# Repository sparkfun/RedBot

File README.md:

SparkFun RedBot
===============

<table class="table table-hover table-striped table-bordered">
  <tr align="center">
   <td></td>
   <td></td>
  </tr>
  <tr align="center">
    <td>RedBot Mainboard [<a href="https://www.sparkfun.com/products/12097">ROB-12097</a>]</td>
    <td>SparkFun Inventor's Kit for RedBot [<a href="https://www.sparkfun.com/products/12649">ROB-12649</a>]</td>
  </tr>
</table>

Design files and firmware files for the [RedBot Main board](https://www.sparkfun.com/products/11622).

Repository Contents
-------------------

* **/Documentation** - Documentation for the library's public API
* **/Hardware** - Eagle PCB layout files
* **/Libraries/Arduino/RedBot** - RedBot support library
* **/Production** - Files to support SparkFun production

Documentation
--------------

* **[Installing an Arduino Library Guide](https://learn.sparkfun.com/tutorials/installing-an-arduino-library)** - Basic information on how to install an Arduino library.
* **[Product Repository](https://github.com/sparkfun/RedBot)** - Main repository (including hardware files) for the RedBot.
* **[Library Repository](https://github.com/sparkfun/SparkFun_Redbot_Arduino_Library)** - Arduino library for the RedBot.
* **[Assembly Guide](https://learn.sparkfun.com/tutorials/assembly-guide-for-redbot-with-shadow-chassis)** - Basic hookup guide for the RedBot.
* **[Experiment Guide](https://learn.sparkfun.com/tutorials/experiment-guide-for-redbot-with-shadow-chassis)** - Experiment guide for the RedBot.

Product Versions
----------------
This repository only contains the hardware files for the RedBot Main board. There are several different support products available for the RedBot Kit however.

* [ROB-12097](https://www.sparkfun.com/products/12097) - RedBot Main Board.
* [ROB-12649](https://www.sparkfun.com/products/12649) - RedBot SparkFun Inventor's Kit
* *[ROB-13166 (RETIRED)](https://www.sparkfun.com/products/13166) - RedBot Basic Kit*
* [ROB-12567](https://www.sparkfun.com/products/12567) - RedBot Buzzer
* [SEN-11999](https://www.sparkfun.com/products/11999) - RedBot Mechanical Bumper
* [SEN-12589](https://www.sparkfun.com/products/12589) - RedBot Accelerometer
* [SEN-11769](https://www.sparkfun.com/products/11769) - RedBot Line Sensor
* [SEN-13582](https://www.sparkfun.com/products/13582) - SparkFun Line Follower Array

License Information
-------------------

This product is _**open source**_! 

Please review the LICENSE.md file for license information. 

If you have any questions or concerns on licensing, please contact techsupport@sparkfun.com.

Distributed as-is; no warranty is given.

- Your friends at SparkFun.

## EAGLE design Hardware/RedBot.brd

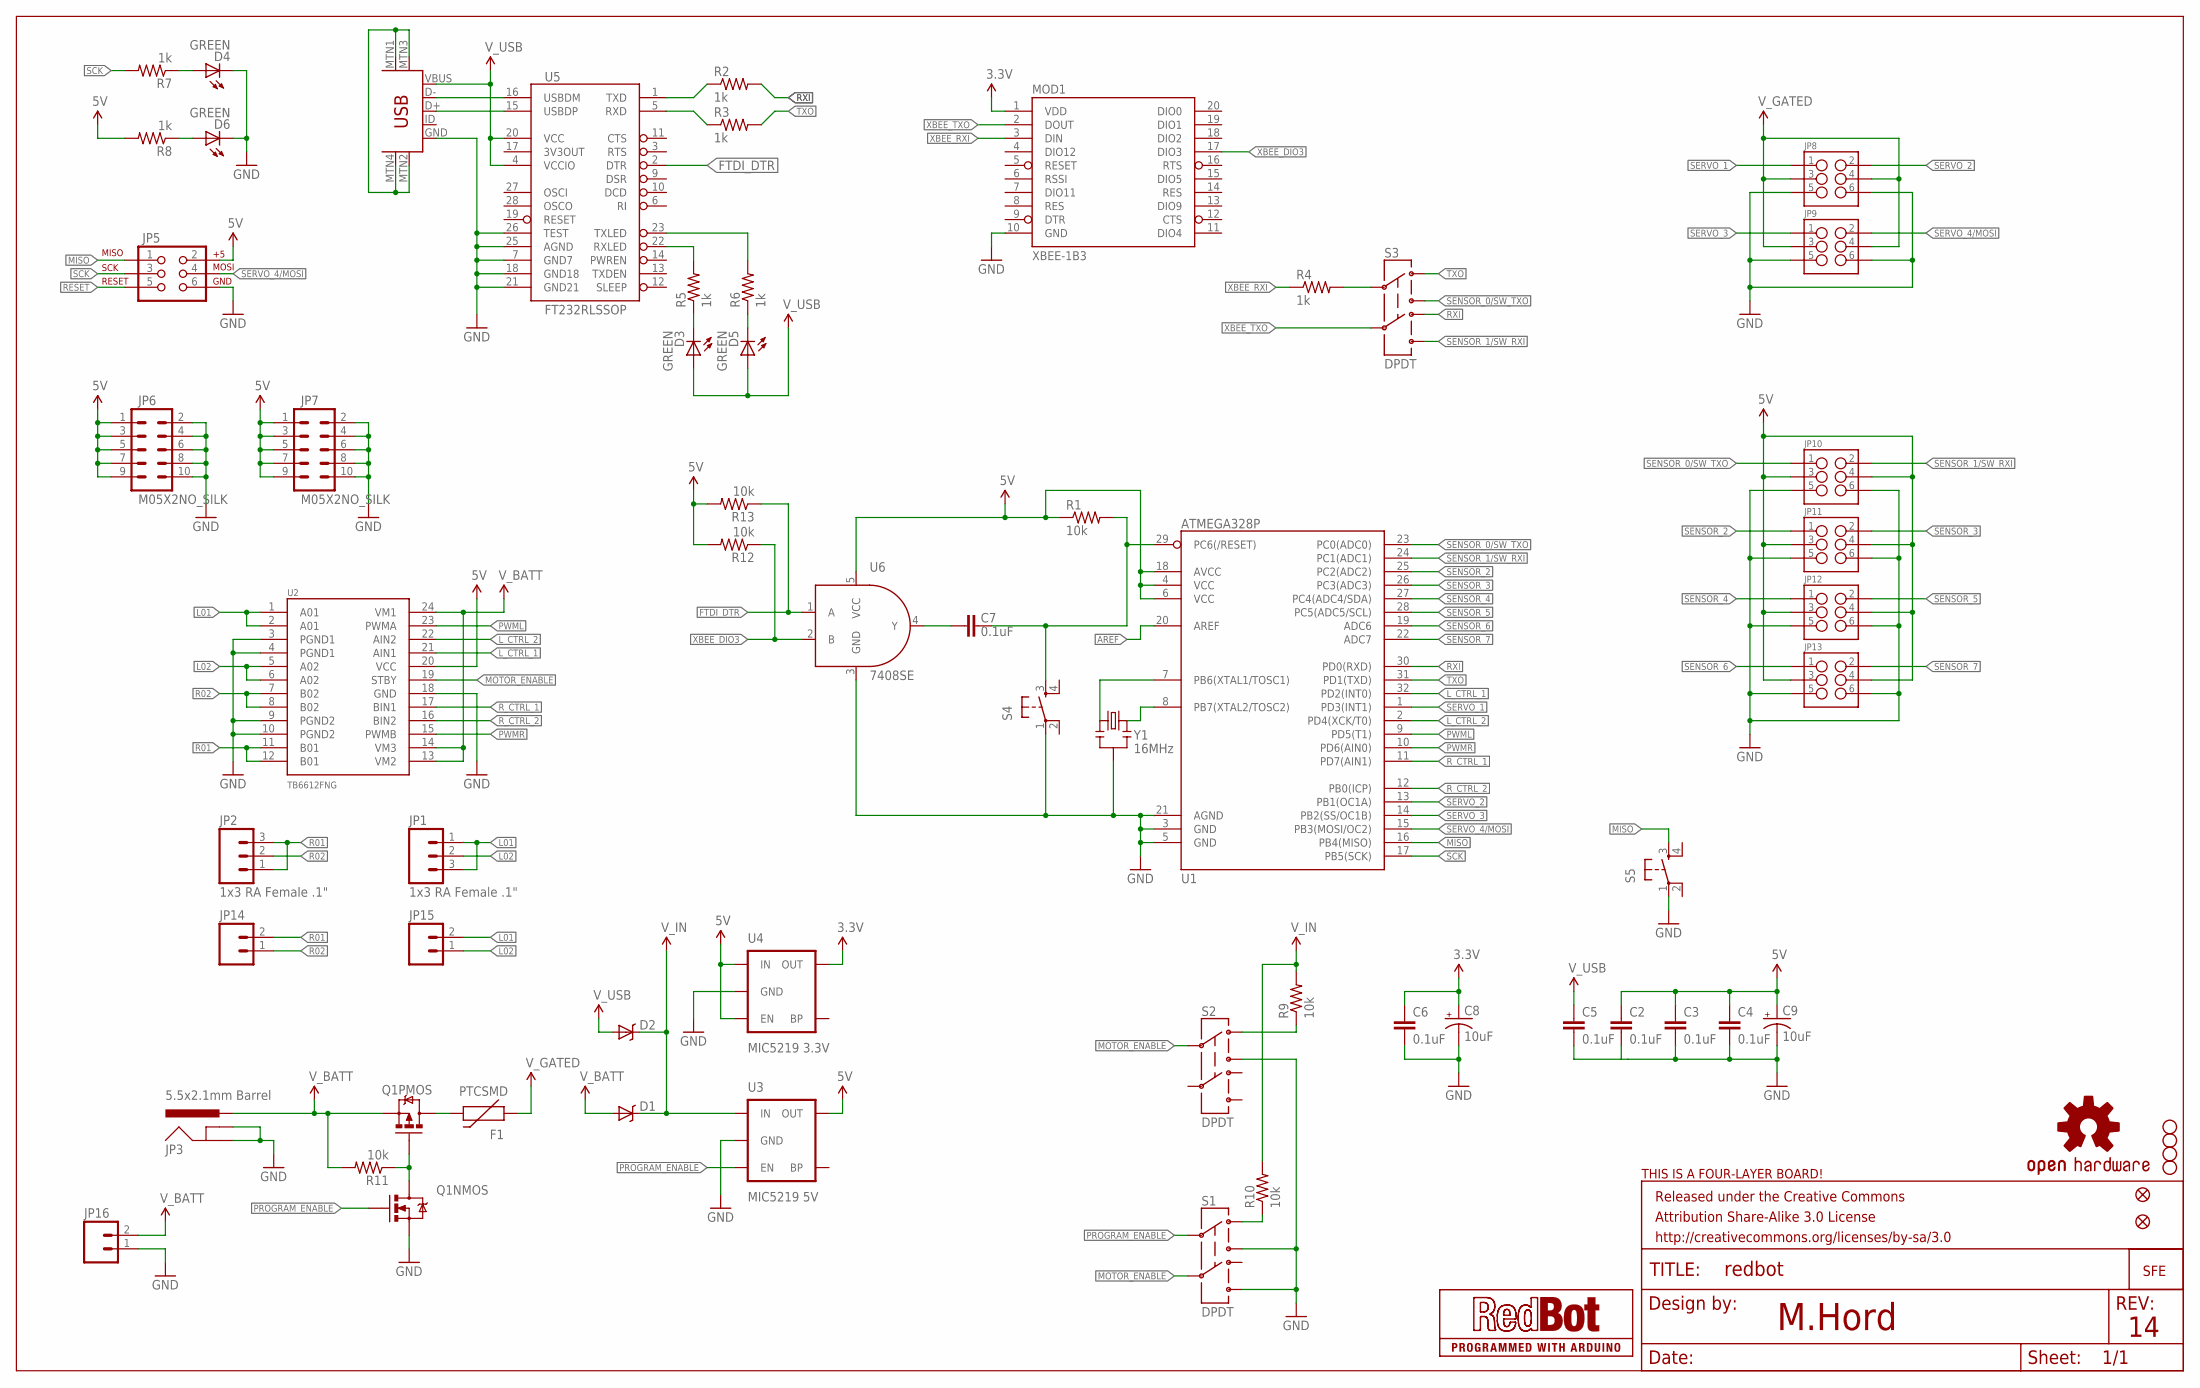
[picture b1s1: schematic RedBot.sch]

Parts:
C2, C3, C4, C5, C6, C7: 0.1uF; 0603-CAP
C8, C9: 10uF; EIA3216
D1, D2: B340A; SMA-DIODE
D3, D4, D5, D6: GREEN; LED-0603
F1: PTCSMD; PTC-1206
FID1, FID2: FIDUCIALUFIDUCIAL; MICRO-FIDUCIAL
FRAME1: FRAME-LETTER; CREATIVE_COMMONS
JP1, JP2: 1x3 RA Female .1"; 1X03_SMD_RA_FEMALE
JP3: 5.5x2.1mm Barrel; POWER_JACK_SMD
JP4: USB-B; USB-MINIB
JP5: AVR_SPI_PRG_6PTH; 2X3
JP6, JP7: M05X2NO_SILK; 2X5_NOSILK
JP8, JP9, JP10, JP11, JP12, JP13: M03X2SMT; 2X3_SMT_POSTS
JP14, JP15, JP16: M02PTH; 1X02
MOD1: XBEE-1B3; XBEE-SMD
Q1: IRF7509; MSOP8
R1, R9, R10, R11, R12, R13: 10k; 0603-RES
R2, R3, R4, R5, R6, R7, R8: 1k; 0603-RES
S1, S2, S3: DPDT; AYZ0202
S4, S5: TAC_SWITCHSMD; TACTILE_SWITCH_SMD
SFE-LOGO1: LOGO-SFENEW; SFE-NEW-WEBLOGO
STANDOFF1, STANDOFF2, STANDOFF3, STANDOFF4: STAND-OFF
U1: ATMEGA328P; TQFP32-08
U2: TB6612FNG; SSOP24
U3: MIC5219 5V; SOT23-5
U4: MIC5219 3.3V; SOT23-5
U5: FT232RLSSOP; SSOP28DB
U6: 7408SE; SOT353
U$17: OSHW-LOGOS; OSHW-LOGO-S
U$21: FOUR_LAYER_WARNING
U$23: REDBOT_LOGO
Y1: 16MHz; RESONATOR-SMD

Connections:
3.3V: C6.1, C8.A (+), MOD1.1 (VDD), U4.5 (OUT)
5V: C2.1, C3.1, C4.1, C9.A (+), JP5.2, JP6.1, JP6.3, JP6.5, JP6.7, JP6.9, JP7.1, JP7.3, JP7.5, JP7.7, JP7.9, JP10.3, JP10.4, JP11.3, JP11.4, JP12.3, JP12.4, JP13.3, JP13.4, R1.1, R8.2, R12.2, R13.2, U1.4 (VCC), U1.6 (VCC), U1.18 (AVCC), U2.20 (VCC), U3.5 (OUT), U4.1 (IN), U4.3 (EN), U6.5 (VCC)
AREF: U1.20 (AREF)
FT232_RXI: R3.1, U5.5 (RXD)
FT232_TXO: R2.1, U5.1 (TXD)
FTDI_DTR: R13.1, U5.2 (DTR), U6.1 (A)
GND: C2.2, C3.2, C4.2, C5.2, C6.2, C8.C (-), C9.C (-), D4.C, D6.C, JP3.GND (GNDBREAK), JP3.P$4 (GND), JP4.GND, JP5.6, JP6.2, JP6.4, JP6.6, JP6.8, JP6.10, JP7.2, JP7.4, JP7.6, JP7.8, JP7.10, JP8.5, JP8.6, JP9.5, JP9.6, JP10.5, JP10.6, JP11.5, JP11.6, JP12.5, JP12.6, JP13.5, JP13.6, JP16.1, MOD1.10 (GND), Q1.1 (S), S1.3, S1.6, S2.3, S4.1, S5.1, U1.3 (GND), U1.5 (GND), U1.21 (AGND), U2.3 (PGND1), U2.4 (PGND1), U2.9 (PGND2), U2.10 (PGND2), U2.18 (GND), U3.2 (GND), U4.2 (GND), U5.7 (GND7), U5.18 (GND18), U5.21 (GND21), U5.25 (AGND), U5.26 (TEST), U6.3 (GND), Y1.2
L01: JP1.1, JP1.3, JP15.2, U2.1 (A01), U2.2 (A01)
L02: JP1.2, JP15.1, U2.5 (A02), U2.6 (A02)
L_CTRL_1: U1.32 (PD2(INT0)), U2.21 (AIN1)
L_CTRL_2: U1.2 (PD4(XCK/T0)), U2.22 (AIN2)
MISO: JP5.1, S5.3, U1.16 (PB4(MISO))
MOTOR_ENABLE: S1.5, S2.2, U2.19 (STBY)
unnamed: R4.2, S3.2
unnamed: Q1.4 (G), Q1.7 (D), Q1.8 (D), R11.1
unnamed: D5.C, R6.1
unnamed: D3.C, R5.1
unnamed: C7.2, U6.4 (Y)
unnamed: JP4.MTN1 (MTN2), JP4.MTN2 (MTN3), JP4.MTN3 (MTN1), JP4.MTN4
unnamed: D4.A, R7.1
unnamed: D6.A, R8.1
unnamed: F1.2, Q1.5 (D), Q1.6 (D)
unnamed: R9.1, S2.1
unnamed: U1.8 (PB7(XTAL2/TOSC2)), Y1.3
unnamed: U1.7 (PB6(XTAL1/TOSC1)), Y1.1
unnamed: JP4.D-, U5.16 (USBDM)
unnamed: JP4.D+, U5.15 (USBDP)
PG_EN: R10.1, S1.1
PROGRAM_ENABLE: Q1.2 (G), S1.2, U3.3 (EN)
PWML: U1.9 (PD5(T1)), U2.23 (PWMA)
PWMR: U1.10 (PD6(AIN0)), U2.15 (PWMB)
R01: JP2.1, JP2.3, JP14.2, U2.11 (B01), U2.12 (B01)
R02: JP2.2, JP14.1, U2.7 (B02), U2.8 (B02)
RESET: C7.1, JP5.5, R1.2, S4.3, U1.29 (PC6(/RESET))
RXI: R2.2, S3.4, U1.30 (PD0(RXD))
RXLED: R5.2, U5.22 (RXLED)
R_CTRL_1: U1.11 (PD7(AIN1)), U2.17 (BIN1)
R_CTRL_2: U1.12 (PB0(ICP)), U2.16 (BIN2)
SCK: JP5.3, R7.2, U1.17 (PB5(SCK))
SENSOR_0/SW_TXO: JP10.1, S3.3, U1.23 (PC0(ADC0))
SENSOR_1/SW_RXI: JP10.2, S3.6, U1.24 (PC1(ADC1))
SENSOR_2: JP11.1, U1.25 (PC2(ADC2))
SENSOR_3: JP11.2, U1.26 (PC3(ADC3))
SENSOR_4: JP12.1, U1.27 (PC4(ADC4/SDA))
SENSOR_5: JP12.2, U1.28 (PC5(ADC5/SCL))
SENSOR_6: JP13.1, U1.19 (ADC6)
SENSOR_7: JP13.2, U1.22 (ADC7)
SERVO_1: JP8.1, U1.1 (PD3(INT1))
SERVO_2: JP8.2, U1.13 (PB1(OC1A))
SERVO_3: JP9.1, U1.14 (PB2(SS/OC1B))
SERVO_4/MOSI: JP5.4, JP9.2, U1.15 (PB3(MOSI/OC2))
TXLED: R6.2, U5.23 (TXLED)
TXO: R3.2, S3.1, U1.31 (PD1(TXD))
V_BATT: D1.A, JP3.VIN0 (PWR), JP16.2, Q1.3 (S), R11.2, U2.13 (VM2), U2.14 (VM3), U2.24 (VM1)
V_GATED: F1.1, JP8.3, JP8.4, JP9.3, JP9.4
V_IN: D1.C, D2.C, R9.2, R10.2, U3.1 (IN)
V_USB: C5.1, D2.A, D3.A, D5.A, JP4.VBUS, U5.4 (VCCIO), U5.20 (VCC)
XBEE_DIO3: MOD1.17 (DIO3), R12.1, U6.2 (B)
XBEE_RXI: MOD1.3 (DIN), R4.1
XBEE_TXO: MOD1.2 (DOUT), S3.5

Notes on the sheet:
M.Hord

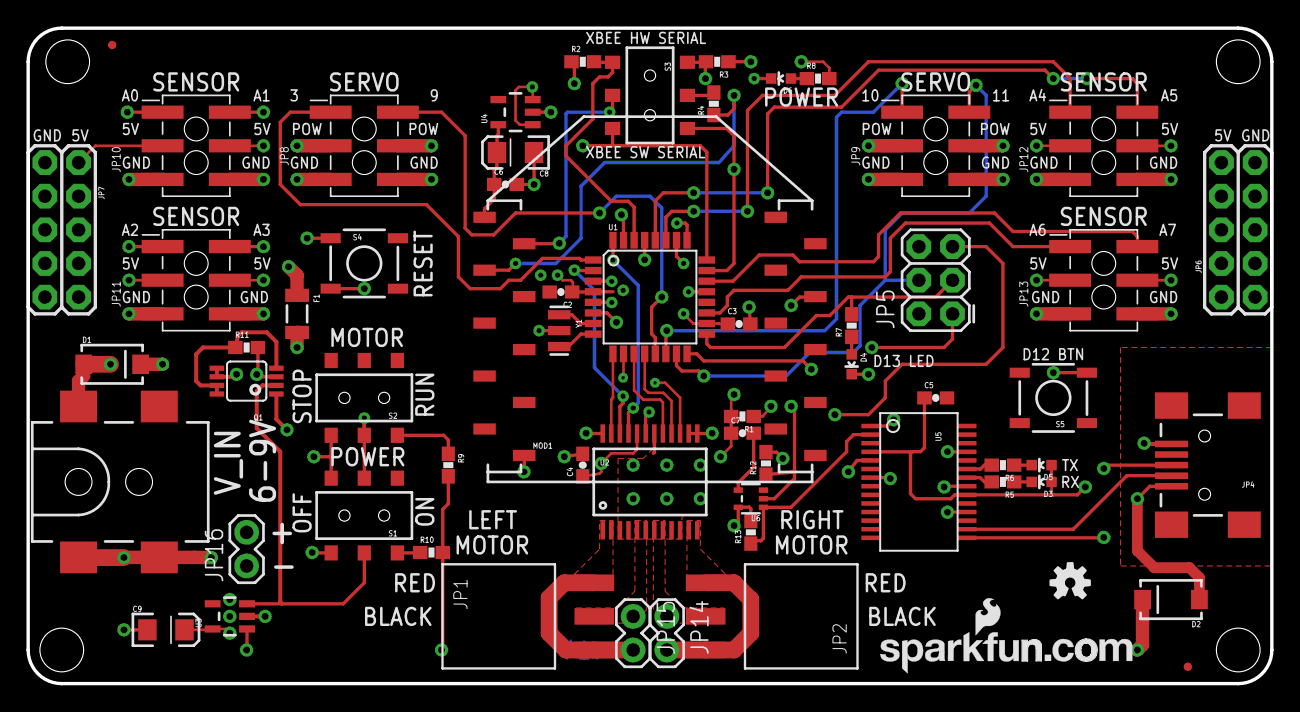
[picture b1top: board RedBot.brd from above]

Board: 4 copper layers, 94.0 x 49.5 mm, 69 parts (1 on the bottom side), 59 nets.

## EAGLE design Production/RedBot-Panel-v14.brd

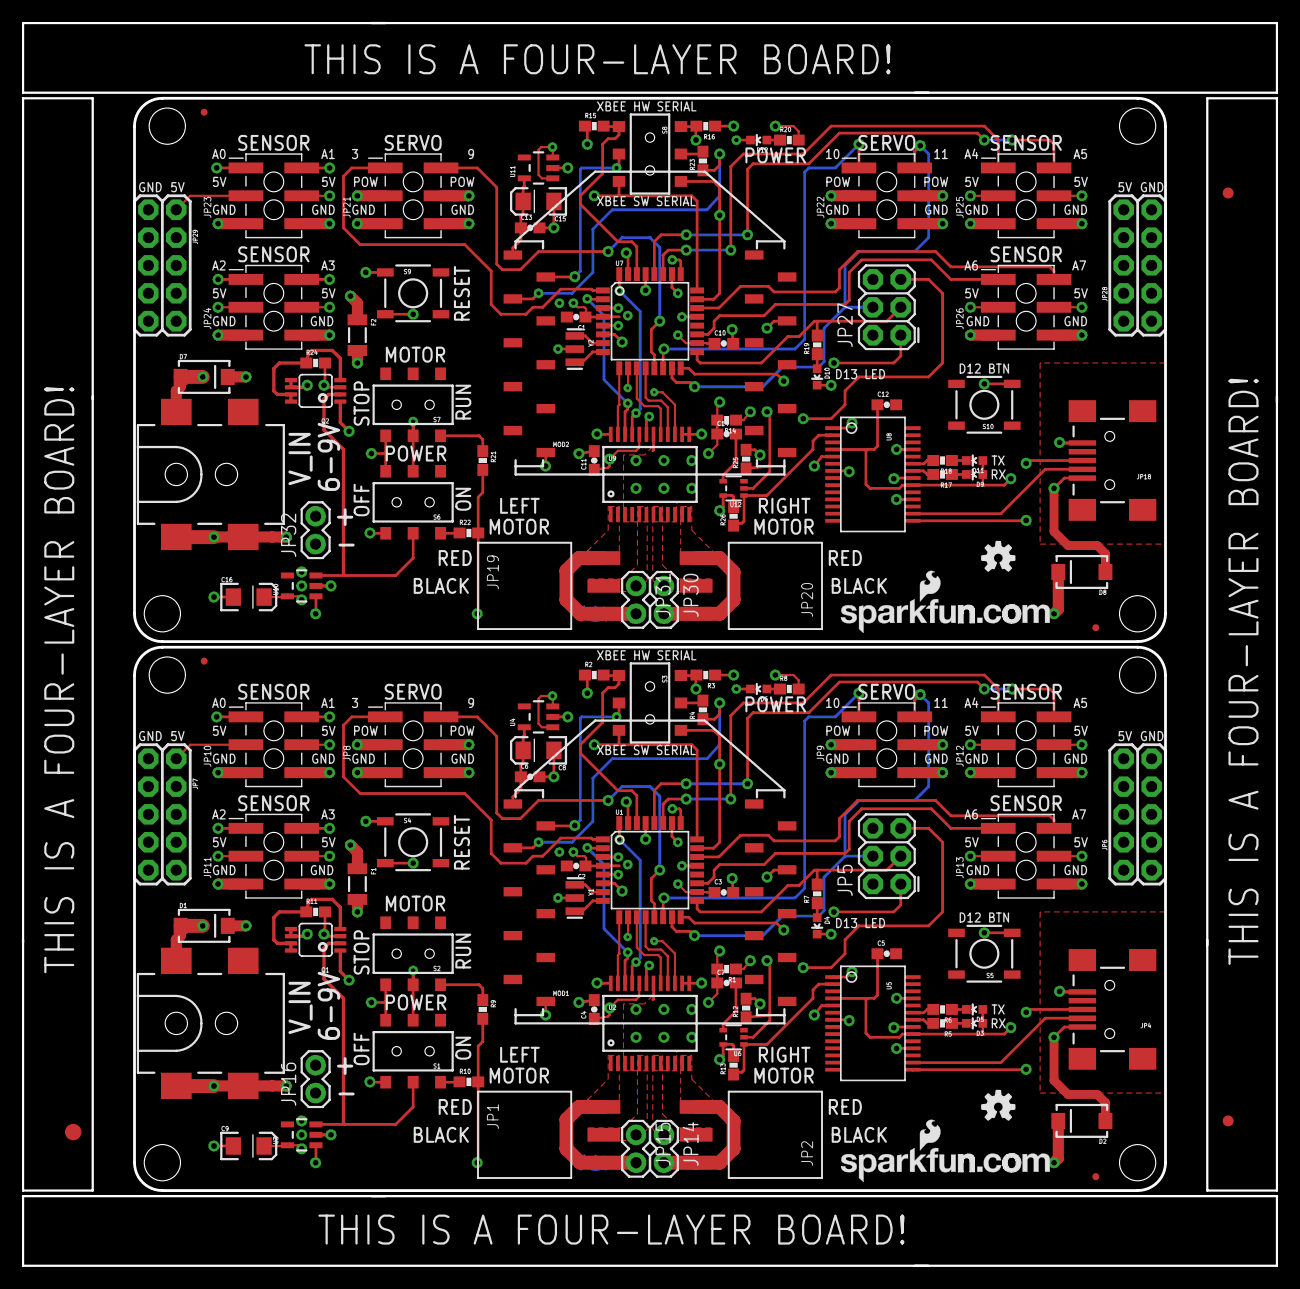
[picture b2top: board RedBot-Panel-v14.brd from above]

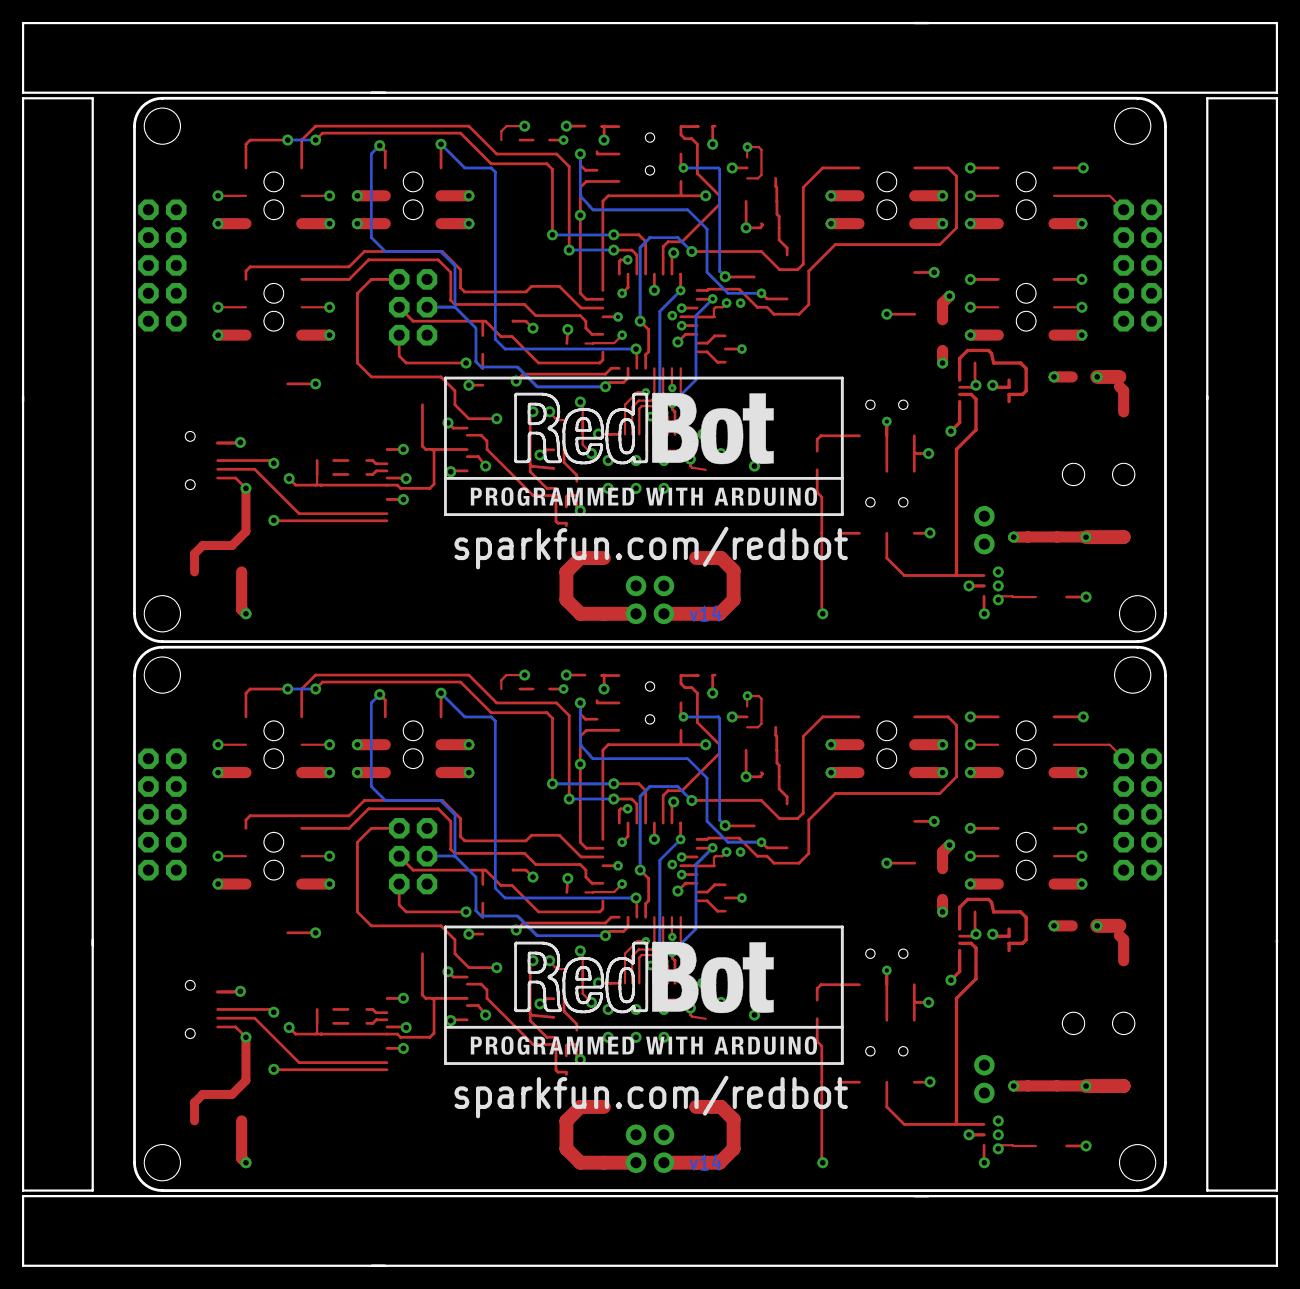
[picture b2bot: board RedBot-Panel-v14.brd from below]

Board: 4 copper layers, 114.3 x 113.3 mm, 137 parts (2 on the bottom side), 118 nets.

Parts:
C1, C2, C3, C4, C5, C6, C7, C10, C11, C12, C13, C14: 0.1uF; 0603-CAP
C8, C9, C15, C16: 10uF; EIA3216
D1, D2, D7, D8: SMA-DIODE
D3, D4, D5, D6, D9, D10, D11, D12: GREEN; LED-0603
E$1: FIDUCIAL-1.5X3
E$2, E$6: FIDUCIAL-1X2
F1, F2: PTCSMD; PTC-1206
FID1, FID2, FID3, FID4: FIDUCIALUFIDUCIAL; MICRO-FIDUCIAL
JP1, JP2, JP19, JP20: 1x3 RA Female .1"; 1X03_SMD_RA_FEMALE
JP3, JP17: 5.5x2.1mm Barrel; POWER_JACK_SMD
JP4, JP18: USB-B; USB-MINIB
JP5, JP27: AVR_SPI_PRG_6PTH; 2X3
JP6, JP7, JP28, JP29: M05X2NO_SILK; 2X5_NOSILK
JP8, JP9, JP10, JP11, JP12, JP13, JP21, JP22, JP23, JP24, JP25, JP26: 2X3_SMT_POSTS
JP14, JP15, JP16, JP30, JP31, JP32: 1X02
MOD1, MOD2: XBEE-1B3; XBEE-SMD
Q1, Q2: MSOP8
R1, R9, R10, R11, R12, R13, R14, R21, R22, R24, R25, R26: 10k; 0603-RES
R2, R3, R4, R5, R6, R7, R8, R15, R16, R17, R18, R19, R20, R23: 1k; 0603-RES
S1, S2, S3, S6, S7, S8: DPDT; AYZ0202
S4, S5, S9, S10: TACTILE_SWITCH_SMD
SFE-LOGO1, SFE-LOGO2: LOGO-SFENEW; SFE-NEW-WEBLOGO
STANDOFF1, STANDOFF2, STANDOFF3, STANDOFF4, STANDOFF5, STANDOFF6, STANDOFF7, STANDOFF8: STAND-OFF
U1, U7: ATMEGA328P; TQFP32-08
U2, U9: TB6612FNG; SSOP24
U3, U10: MIC5219 5V; SOT23-5
U4, U11: MIC5219 3.3V; SOT23-5
U5, U8: FT232RLSSOP; SSOP28DB
U6, U12: 7408SE; SOT353
U$1, U$17: OSHW-LOGOS; OSHW-LOGO-S
U$2, U$23: REDBOT_LOGO
Y1, Y2: 16MHz; RESONATOR-SMD

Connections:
3.3V: C6.1, C8.A, MOD1.1, U4.5
3.3V1: C13.1, C15.A, MOD2.1, U11.5
5V: C2.1, C3.1, C4.1, C9.A, JP5.2, JP6.1, JP6.3, JP6.5, JP6.7, JP6.9, JP7.1, JP7.3, JP7.5, JP7.7, JP7.9, JP10.3, JP10.4, JP11.3, JP11.4, JP12.3, JP12.4, JP13.3, JP13.4, R1.1, R8.2, R12.2, R13.2, U1.4, U1.6, U1.18, U2.20, U3.5, U4.1, U4.3, U6.5
5V1: C1.1, C10.1, C11.1, C16.A, JP23.3, JP23.4, JP24.3, JP24.4, JP25.3, JP25.4, JP26.3, JP26.4, JP27.2, JP28.1, JP28.3, JP28.5, JP28.7, JP28.9, JP29.1, JP29.3, JP29.5, JP29.7, JP29.9, R14.1, R20.2, R25.2, R26.2, U7.4, U7.6, U7.18, U9.20, U10.5, U11.1, U11.3, U12.5
FT232_RXI: R3.1, U5.5
FT232_RXI1: R16.1, U8.5
FT232_TXO: R2.1, U5.1
FT232_TXO1: R15.1, U8.1
FTDI_DTR: R13.1, U5.2, U6.1
FTDI_DTR1: R26.1, U8.2, U12.1
GND: C2.2, C3.2, C4.2, C5.2, C6.2, C8.C, C9.C, D4.C, D6.C, JP3.GND, JP3.P$4, JP4.GND, JP5.6, JP6.2, JP6.4, JP6.6, JP6.8, JP6.10, JP7.2, JP7.4, JP7.6, JP7.8, JP7.10, JP8.5, JP8.6, JP9.5, JP9.6, JP10.5, JP10.6, JP11.5, JP11.6, JP12.5, JP12.6, JP13.5, JP13.6, JP16.1, MOD1.10, Q1.1, S1.3, S1.6, S2.3, S4.1, S5.1, U1.3, U1.5, U1.21, U2.3, U2.4, U2.9, U2.10, U2.18, U3.2, U4.2, U5.7, U5.18, U5.21, U5.25, U5.26, U6.3, Y1.2
GND1: C1.2, C10.2, C11.2, C12.2, C13.2, C15.C, C16.C, D10.C, D12.C, JP17.GND, JP17.P$4, JP18.GND, JP21.5, JP21.6, JP22.5, JP22.6, JP23.5, JP23.6, JP24.5, JP24.6, JP25.5, JP25.6, JP26.5, JP26.6, JP27.6, JP28.2, JP28.4, JP28.6, JP28.8, JP28.10, JP29.2, JP29.4, JP29.6, JP29.8, JP29.10, JP32.1, MOD2.10, Q2.1, S6.3, S6.6, S7.3, S9.1, S10.1, U7.3, U7.5, U7.21, U8.7, U8.18, U8.21, U8.25, U8.26, U9.3, U9.4, U9.9, U9.10, U9.18, U10.2, U11.2, U12.3, Y2.2
L01: JP1.1, JP1.3, JP15.2, U2.1, U2.2
L02: JP1.2, JP15.1, U2.5, U2.6
L03: JP19.1, JP19.3, JP31.2, U9.1, U9.2
L04: JP19.2, JP31.1, U9.5, U9.6
L_CTRL_1: U1.32, U2.21
L_CTRL_2: U1.2, U2.22
L_CTRL_3: U7.2, U9.22
L_CTRL_4: U7.32, U9.21
MISO: JP5.1, S5.3, U1.16
MISO1: JP27.1, S10.3, U7.16
MOTOR_ENABLE: S1.5, S2.2, U2.19
MOTOR_ENABLE1: S6.5, S7.2, U9.19
unnamed: R4.2, S3.2
unnamed: Q1.4, Q1.7, Q1.8, R11.1
unnamed: D5.C, R6.1
unnamed: D3.C, R5.1
unnamed: C7.2, U6.4
unnamed: JP4.MTN1, JP4.MTN2, JP4.MTN3, JP4.MTN4
unnamed: D4.A, R7.1
unnamed: D6.A, R8.1
unnamed: F1.2, Q1.5, Q1.6
unnamed: JP18.D-, U8.16
unnamed: JP18.D+, U8.15
unnamed: U7.8, Y2.3
unnamed: U7.7, Y2.1
unnamed: D10.A, R19.1
unnamed: D12.A, R20.1
unnamed: R21.1, S7.1
unnamed: C14.2, U12.4
unnamed: R9.1, S2.1
unnamed: R23.2, S8.2
unnamed: JP18.MTN1, JP18.MTN2, JP18.MTN3, JP18.MTN4
unnamed: Q2.4, Q2.7, Q2.8, R24.1
unnamed: D11.C, R18.1
unnamed: U1.8, Y1.3
unnamed: U1.7, Y1.1
unnamed: D9.C, R17.1
unnamed: JP4.D-, U5.16
unnamed: JP4.D+, U5.15
unnamed: F2.2, Q2.5, Q2.6
PG_EN: R10.1, S1.1
PG_EN1: R22.1, S6.1
PROGRAM_ENABLE: Q1.2, S1.2, U3.3
PROGRAM_ENABLE1: Q2.2, S6.2, U10.3
PWML: U1.9, U2.23
PWML1: U7.9, U9.23
PWMR: U1.10, U2.15
PWMR1: U7.10, U9.15
R01: JP2.1, JP2.3, JP14.2, U2.11, U2.12
R02: JP2.2, JP14.1, U2.7, U2.8
R03: JP20.2, JP30.1, U9.7, U9.8
R04: JP20.1, JP20.3, JP30.2, U9.11, U9.12
RESET: C7.1, JP5.5, R1.2, S4.3, U1.29
RESET1: C14.1, JP27.5, R14.2, S9.3, U7.29
RXI: R2.2, S3.4, U1.30
RXI1: R15.2, S8.4, U7.30
RXLED: R5.2, U5.22
RXLED1: R17.2, U8.22
R_CTRL_1: U1.11, U2.17
R_CTRL_2: U1.12, U2.16
R_CTRL_3: U7.11, U9.17
R_CTRL_4: U7.12, U9.16
SCK: JP5.3, R7.2, U1.17
SCK1: JP27.3, R19.2, U7.17
SENSOR_0/SW_TXO: JP10.1, S3.3, U1.23
SENSOR_0/SW_TXO1: JP23.1, S8.3, U7.23
SENSOR_1: JP24.1, U7.25
SENSOR_1/SW_RXI: JP10.2, S3.6, U1.24
SENSOR_1/SW_RXI1: JP23.2, S8.6, U7.24
SENSOR_2: JP11.1, U1.25
SENSOR_3: JP11.2, U1.26
SENSOR_4: JP12.1, U1.27
SENSOR_5: JP12.2, U1.28
SENSOR_6: JP13.1, U1.19
SENSOR_7: JP13.2, U1.22
SENSOR_8: JP24.2, U7.26
SENSOR_9: JP25.1, U7.27
SENSOR_10: JP25.2, U7.28
SENSOR_11: JP26.1, U7.19
SENSOR_12: JP26.2, U7.22
SERVO_1: JP8.1, U1.1
SERVO_2: JP8.2, U1.13
SERVO_3: JP9.1, U1.14
SERVO_4: JP21.1, U7.1
SERVO_4/MOSI: JP5.4, JP9.2, U1.15
SERVO_4/MOSI1: JP22.2, JP27.4, U7.15
SERVO_5: JP21.2, U7.13
SERVO_6: JP22.1, U7.14
TXLED: R6.2, U5.23
TXLED1: R18.2, U8.23
TXO: R3.2, S3.1, U1.31
TXO1: R16.2, S8.1, U7.31
V_BATT: D1.A, JP3.VIN0, JP16.2, Q1.3, R11.2, U2.13, U2.14, U2.24
V_BATT1: D7.A, JP17.VIN0, JP32.2, Q2.3, R24.2, U9.13, U9.14, U9.24
V_GATED: F1.1, JP8.3, JP8.4, JP9.3, JP9.4
V_GATED1: F2.1, JP21.3, JP21.4, JP22.3, JP22.4
V_IN: D1.C, D2.C, R9.2, R10.2, U3.1
V_IN1: D7.C, D8.C, R21.2, R22.2, U10.1
V_USB: C5.1, D2.A, D3.A, D5.A, JP4.VBUS, U5.4, U5.20
V_USB1: C12.1, D8.A, D9.A, D11.A, JP18.VBUS, U8.4, U8.20
XBEE_DIO1: MOD2.17, R25.1, U12.2
XBEE_DIO3: MOD1.17, R12.1, U6.2
XBEE_RXI: MOD1.3, R4.1
XBEE_RXI1: MOD2.3, R23.1
XBEE_TXO: MOD1.2, S3.5
XBEE_TXO1: MOD2.2, S8.5

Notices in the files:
parts and their libraries:
SparkFun-Aesthetics: Licensing: CC v3.0 Share-Alike You are welcome to use this library for commercial purposes.
SparkFun-Aesthetics: Released under the Creative Commons Attribution Share-Alike 3.0 License
SparkFun-Aesthetics: http://creativecommons.org/licenses/by-sa/3.0
